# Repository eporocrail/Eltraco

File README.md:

Aim is to develop a switching and signaling system for model railroad track control.
  Communication is wireless.

  To disconnect the decoder from the controlling software in space and time the MOSQUITTO
  MQTT broker is used.

  Hardware setup is as simple as possible. In stead of having one hardware module for diffferent applications
  the design aims for three different PCB's specific to task where the Wemos has to be slotted into.

  Sofware is modularised. It is gathered into one software package. The functionality of each separate decoder
  is configured by means of a website genrated by the decoder.

  *********************************************************************************************

  Target platform is Wemos D1 mini.

  11 digital input/output pins, all pins have interrupt/pwm/I2C/one-wire supported(except D0)
  1 analog input(3.2V max input)
  a Micro USB connection
  compatible with Arduino IDE.
  pins are active LOW but the Arduino IDE inverts this.

  All of the IO pins run at 3.3V:
  A levelshifter or voltage divider is required.

  For a relay a pin is followed by a transistor/IC. A relay is driven with 5V.

  For a sensor or servo each pin is followed by a 330R resistor to limit current to 10 mA.

  eltraco decoder     Function

  eltraco sensor decoder    Scanning 9 sensors
  eltraco switch decoder    Controlling 8 outputs
  eltraco turnout decoder   Controlling 2 turnouts

  GPIO usage:

  Decoder  pins     function

  Sensor   D0 .. D7     digital sensor
  
           A0           analogue sensor

  Switch   D0 .. D7     output (switch)

  Double   D0    relais 1
  
  Turnout  D1    current detector 1
           
           D2    current detector 2
           
           D3    not used
           
           D4    not used
           
           D5    relais 2
           
           D6    servo 1
           
           D7    servo 2
           
           D8    not used
           
           A0    not used
           
  Single   D0    relais 1
  
  Turnout  D1    current detector 1
           
           D2    sensor
           
           D3    sensor
           
           D4    sensor
           
           D5    sensor
           
           D6    servo 1
           
           D7    not used
           
           D8    not used
           
           A0    not used         

  ROCNET PROTOCOL

  packet payload content:
  byte 1  : groupId
  
  byte 2  : receiveIdH
  
  byte 3  : receiveIdL
  
  byte 4  : sendIdH
  
  byte 5  : sendIdL
  
  byte 6  : group
  
  byte 7  : code
  
  byte 8  : length
  
  byte 9  : data1
  
  byte 10 : data2
  
  byte 11 : data3
  
  byte 12 : data4

  --byte 1 only used for large network. Normally 0.

  --byte 2 only used when more than 255 decoders. Normally 0.

  --byte 3 Rocrail Server default Id is 1

  Broadcast Id = 0
  
  Decoder   Id = 2 ... 255   Not used for switching decoder

  --byte 4 only used when more than 255 decoders. Normally 0.

  --byte 5 Rocrail Server default Id is 1

  Decoder Id   = 2 ... 255 with restrictions as described under "addressing"

  --byte 6

  groups
  code   description     remark                     MQTT topic
  
  0      Host            Rocrail                    rocnet/ht
  
  7      Clock Fast      Clock                      rocnet/ck
  
  8      Sensor          Position determination     rocnet/sr
  
  9      Output                                     rocnet/ot

  --byte 7

  Code:  bit 7 = 0
  
     bit 6 and bit 5 represent Type of code
     
     bit 4 .. 0:  5 bit command 0 .. 31

  Type: 0 - test
  
  1 - request
  
  2 - event
  
  3 - reply

  Sensor

  Actions
  code description data 1  data 2  data 3  data 4  data n
  1    report      addrH¹  addrL¹  status  port    identifier (RFID)

  ¹) Address of the reporting loco.
  The sensor ID is set in the header; Sender.

  Output

  Type   Value
  
  switch   0
  
  light    1
  
  servo    2

  Actions
  code description data 1  data 2  data 3
  
  0      off       type    value   address
  
  1      on        type    value   address

  --byte 8 Netto number of following data bytes.

  At a speed of 200 KmH a loc runs 64 mm per second in scale H0 and 35 mm per second in scale N.
  To come to a reliable detection reaction a point sensor must be scanned at least 20 times per second in H0
  and at least 10 times per second in scale N.

  For scale H0 scan delay should be not larger than 50 miliseconds and for scale N not larger
  than 100 miliseconds. Default will be 20.

  The Wemos Module needs no 3.3V power supply. To the 5V pin external powersupply can be connected.

  Addressing:

  Addressing falls apart in a WiFi address, being an IP-address and a Rocnet address.

  Rocnet:

  In the Rocnet protocol (IdH*256 + IdL) represents the Rocnet Node Number. This number ranges from 1 .. 65536.
  It represents the "Bus" number.
  Depending on the function performed the I/O pin of the decoder is addressed with "data3" for
  "output" functions or "data4" for "sensor" functions. Turnouts are controlled with an "output" function.
  The values of data3/data4 are in rocrail inserted in field "Address"

  For eltraco an I/O pin is addressed by the combination of receiveIdL and data3/data4.
  This way each individual pin of each individual decoder can be addressed.

  A second way to address an IO pin is using a "fixed" receiveIdL and discriminating by means of data3/data4.
  Using this method provides in eltraco the possibility to address 255 turnouts by a consecutive number only.
  The default receiveIdL of Rocrail is "9". This receiveIdL is used to control turnouts. These addresses are
  used by the servo-tool to adjust the servo of a turnout.

  IP-address:
  The following IP-adress range is available:
  192.168.xxx.xxx

  IP-addres: Router 192.168.xxx.251
  
             Configuration website 192.168.xxx.252
             
             Command Station       192.168.xxx.253
             
             Mosquitto             192.168.xxx.254

  For the decoders are available 192.168.xxx.2 - 192.168.2.250

  Each decoder is allocated a unique IP-address out of the range 192.168.xxx.2 - 192.168.2.250.
  The last triplet is the Rocrail "Bus" number.

  Single turnout decoder:

Each decoder controls 1 turnout and reports occupation of it.

For the turnout decoder occupation of the turnout is reported at "Address" 1.

Table: Switches tab Interface - the last part of the IP-address is inserted into field "Bus"
       "1" is inserted into field "Address".
       e.g. (192.168.0.154 turnout is inserted as Bus 154 Address 1)

Table: Sensor tab Interface - the last part of the IP-address is inserted into field "Bus"
       "1" is inserted into field "Address". The external sensors report using "Address" numbers 2 .. 5.
       e.g. (192.168.0.154 turnout is inserted as Bus 154 Address 1, the second external sensor of the same
       decoder is inserted as Bus 154 Address 3)

Double turnout decoder:

Each decoder controls 2 turnouts and reports occupation of them.

For the turnout decoder occupation of the first turnout is reported at "Address" 1 and of the second
turnout at "Address" 2.

Table: Switches tab Interface - the last part of the IP-address is inserted into field "Bus"
       For the first turnout "1" is inserted into field "Address". For the second one "2" is inserted
       e.g. (192.168.0.154 turnout 2 is inserted as Bus 154 Address 2)

Table: Sensor tab Interface - the last part of the IP-address is inserted into field "Bus"
       For the first turnout "1" is inserted into field "Address". For the second one "2" is inserted
       e.g. (192.168.0.154 turnout 2 is inserted as Bus 154 Address 2)

Operation

During testing it turned out that move orders from Rocrail arrived so fast that an ongoing movement was
interrupted. To cater for this, incoming turnout orders are stored into a buffer. When ongoing movement is concluded,
buffer content is converted into a turnout order and the next turnout starts moving.

Sensor decoder:
Each decoder has eight digital and one analogue sensor.

The sensors report using "Address" numbers 1 .. 9.
Use of the analogue sensor is to be programmed by the user.

Table: Sensor tab Interface - the last part of the IP-address is inserted into field "Bus"
       port number is inserted into field "Address"
       e.g. (192.168.0.076 sensor 5 is inserted as Bus 76 Address 5)

Operation

The state of the sensor is controlled by interrupt. Not only the state of the sensor but also the point in time of activation is stored.
If the sensor is still in the activated state after the debounce period has passed the Sensor Message is sent. 
The state of the sensor will change to "inactive" by interrupt. After the minimum activation time has passed this inactive state is signalled 
with a Sensor Message.

Interrupt reacts on changes to drive the sensor state.

D0 can NOT be used with Interrupt. This reduces the amount of interrupt driven sensors per module to 7. (D1 .. D7).

D0 has to be watched with "polling".

Switch decoder
Each decoder has eight outputs.

Each decoder is allocated a unique IP-address out of the range 192.168.xxx.2 - 192.168.2.250.
The last triplet is the Rocrail "Bus" number.

The outputs are switched using "Address" numbers 1 .. 8.

Table: Switches tab Interface - the last part of the IP-address is inserted into field "Bus"
       The individual port number is inserted into field "Address"
       e.g. (192.168.0.201 port 3 is inserted as Bus 201 Address 3)

Operation

Via configuration it is possible to have an output switched ON during 200 mSec. An additional relais attached to that
output can be used to control a solenoid activated device.

To signal the state of a switch, a sensor message is transmitted after each switch action. 

Configuration of decoder

The Wemos module can be used in "ST" mode and "AP" mode simultaneously.
In "ST" mode it is possible to login onto an existing WiFi network for normal operations.
In "AP" mode it is possible to generate its own WiFi network. This network is used for configuration of the decoder.
Each module has its own configuration webserver on a shared WiFi configuration network with its own IP address.

The websever is based on the "EmbAJAX" library. This library facilitates dataexchange between webserver on the decoder
and a browser on a client. The user experience is as much as possible comparable with webservers on PC like hardware.

Configuration data and servo angles are stored in EEPROM.
Allocation of EEPROM memory to variables has to be planned.
  location variable
      0    AngleA1
      1    AngleB1
      2    Delay1
      3    Swap1
      4    AngleA2
      5    AngleB2
      6    Delay2
      7    Swap2
      8    decoderType
      9    debugFlag

  GENERALOFFSET+ 0 .. 25 ST WiFi SSID
  
  GENERALOFFSET + SSIDOFFSET + 0 .. 8 ST WiFi Password
  
  GENERALOFFSET + SSIDOFFSET + PWDOFFSET + 0 .. 6 ST WiFi IP address triplets
  
  GENERALOFFSET + SSIDOFFSET + PWDOFFSET + IPOFFSET + 0 .. 8 Output puls 
  
  GENERALOFFSET + SSIDOFFSET + PWDOFFSET + IPOFFSET + OUTPUTOFFSET + 0 .. 8 Switch active puls length
  
  GENERALOFFSET + SSIDOFFSET + PWDOFFSET + IPOFFSET + OUTPUTOFFSET + PULSLENGTHOFFSET+ 0 .. 8 Output sensor message

  GENERALOFFSET      - 20
  SSIDOFFSET         - 30
  PWDOFFSET          - 20
  IPOFFSET           - 10
  OUTPUTOFFSET        -10
  PULSLENGTHOFFSET    -20
  OUTPUTSENSOROFFSET  -10

The ST WiFi password is generated out of "ELTRACO" and the decoderId.
The AP WiFi SSID is generated out of "ELTRACO" and the decoderID. This also aplies to the related password.

There are two ways to transfer Software to the decoder.
Via USB cable and after inital software installation also "Over The Air"(OTA).
Each decoder has its own OTA name which is generated outof "ELTRACO" and the decoderId.

Author: E. Postma

November 2018

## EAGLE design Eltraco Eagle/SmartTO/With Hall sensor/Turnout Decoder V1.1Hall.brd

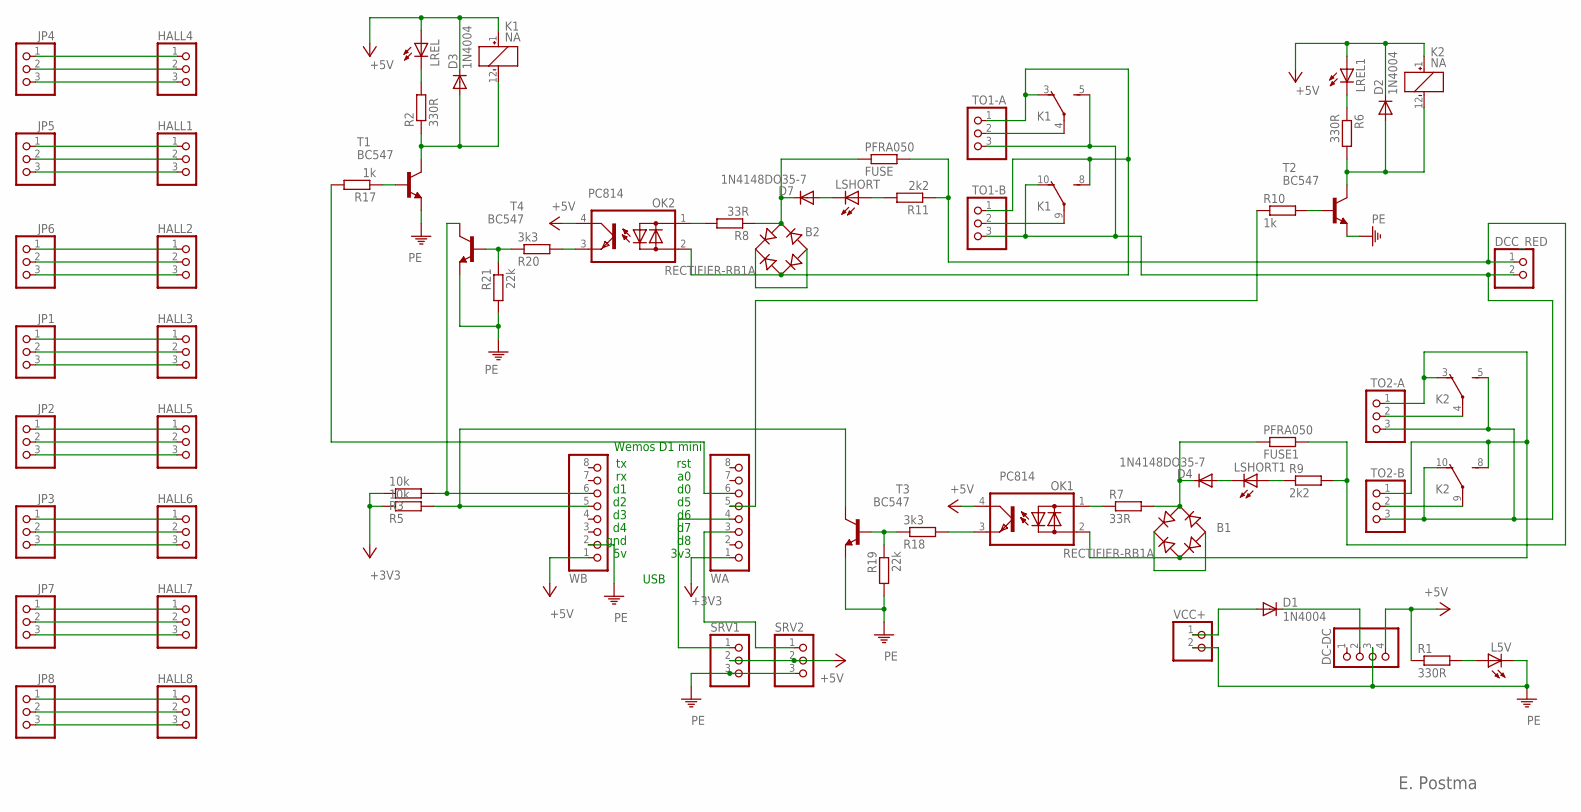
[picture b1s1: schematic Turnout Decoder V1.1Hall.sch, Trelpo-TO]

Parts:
B1, B2: RECTIFIER-RB1A; RB1A
D1, D2, D3: 1N4004; DO41-10
D4, D7: 1N4148DO35-7; DO35-7
DC-DC: PINHD-1X4; 1X04
DCC_RED: PINHD-1X2; 1X02
FUSE, FUSE1: PFRA050; 0414V
HALL1, HALL2, HALL3, HALL4, HALL5, HALL6, HALL7, HALL8: PINHD-1X3; 1X03
JP1, JP2, JP3, JP4, JP5, JP6, JP7, JP8: PINHD-1X3; 1X03
K1, K2: NA
L5V: LED3MM
LREL, LREL1: LED3MM
LSHORT, LSHORT1: LED3MM
OK1, OK2: PC814; DIL04
R1, R2, R6: 330R; 0207/7
R3, R5: 10k; 0207/7
R7, R8: 33R; 0207/7
R9, R11: 2k2; 0207/7
R10, R17: 1k; 0207/7
R18, R20: 3k3; 0207/7
R19, R21: 22k; 0207/7
SRV1, SRV2: PINHD-1X3; 1X03
T1, T2, T3, T4: BC547; TO92
TO1-A, TO1-B, TO2-A, TO2-B: PINHD-1X3; 1X03
VCC+: PINHD-1X2; 1X02
WA: PINHD-1X8; 1X08
WB: PINHD-1X8; 1X08

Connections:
+3V3: R3.1, R5.1, WA.1
+5V: D2.C, D3.C, DC-DC.4, K1.1 (+), K2.1 (+), LREL.A, LREL1.A, OK1.4 (C), OK2.4 (C), R1.1, SRV1.2, SRV2.2, WB.1
unnamed: HALL1.2, JP5.2
unnamed: LREL1.K (C), R6.1
unnamed: DCC_RED.1, FUSE.2, FUSE1.2, R9.2, R11.1
unnamed: D1.A, VCC+.1
unnamed: OK1.1 (AC1), R7.1
unnamed: LSHORT1.A, R9.1
unnamed: D4.A, LSHORT1.K (C)
unnamed: D2.A, K2.12 (-), R6.2, T2.3 (C)
unnamed: R10.2, T2.2 (B)
unnamed: B1.+, B1.-
unnamed: OK1.3 (E), R18.2
unnamed: LREL.K (C), R2.2
unnamed: K2.4, TO2-A.2
unnamed: B2.AC2, K1.3 (O), K1.8 (S), OK2.2 (AC2), TO1-A.1, TO1-B.1
unnamed: K2.9, TO2-B.2
unnamed: DCC_RED.2, K1.5 (S), K1.10 (O), K2.5 (S), K2.10 (O), TO1-A.3, TO1-B.3, TO2-A.3, TO2-B.3
unnamed: OK2.3 (E), R20.2
unnamed: B1.AC2, K2.3 (O), K2.8 (S), OK1.2 (AC2), TO2-A.1, TO2-B.1
unnamed: R3.2, T4.3 (C), WB.6
unnamed: B1.AC1, D4.C, FUSE1.1, R7.2
unnamed: OK2.1 (AC1), R8.2
unnamed: R5.2, T3.3 (C), WB.5
unnamed: B2.AC1, D7.C, FUSE.1, R8.1
unnamed: HALL1.1, JP5.1
unnamed: HALL1.3, JP5.3
unnamed: K1.4, TO1-A.2
unnamed: R18.1, R19.1, T3.2 (B)
unnamed: R20.1, R21.1, T4.2 (B)
unnamed: R17.2, WA.6
unnamed: HALL2.2, JP6.2
unnamed: SRV1.1, WA.4
unnamed: K1.9, TO1-B.2
unnamed: SRV2.1, WA.3
unnamed: R10.1, WA.5
unnamed: LSHORT.A, R11.2
unnamed: HALL2.1, JP6.1
unnamed: HALL2.3, JP6.3
unnamed: HALL3.2, JP1.2
unnamed: HALL3.1, JP1.1
unnamed: HALL3.3, JP1.3
unnamed: D7.A, LSHORT.K (C)
unnamed: B2.+, B2.-
unnamed: HALL5.2, JP2.2
unnamed: HALL5.1, JP2.1
unnamed: HALL5.3, JP2.3
unnamed: L5V.A, R1.2
unnamed: HALL6.2, JP3.2
unnamed: HALL6.1, JP3.1
unnamed: R17.1, T1.2 (B)
unnamed: D3.A, K1.12 (-), R2.1, T1.3 (C)
unnamed: HALL6.3, JP3.3
unnamed: HALL7.2, JP7.2
unnamed: HALL7.1, JP7.1
unnamed: HALL7.3, JP7.3
unnamed: HALL4.2, JP4.2
unnamed: HALL4.3, JP4.3
unnamed: HALL4.1, JP4.1
unnamed: D1.C, DC-DC.2
unnamed: HALL8.2, JP8.2
unnamed: HALL8.1, JP8.1
unnamed: HALL8.3, JP8.3
PE: DC-DC.3, L5V.K (C), R19.2, R21.2, SRV1.3, SRV2.3, T1.1 (E), T2.1 (E), T3.1 (E), T4.1 (E), VCC+.2, WB.2

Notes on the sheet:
rst
3v3
Wemos D1 mini
gnd
USB
E. Postma

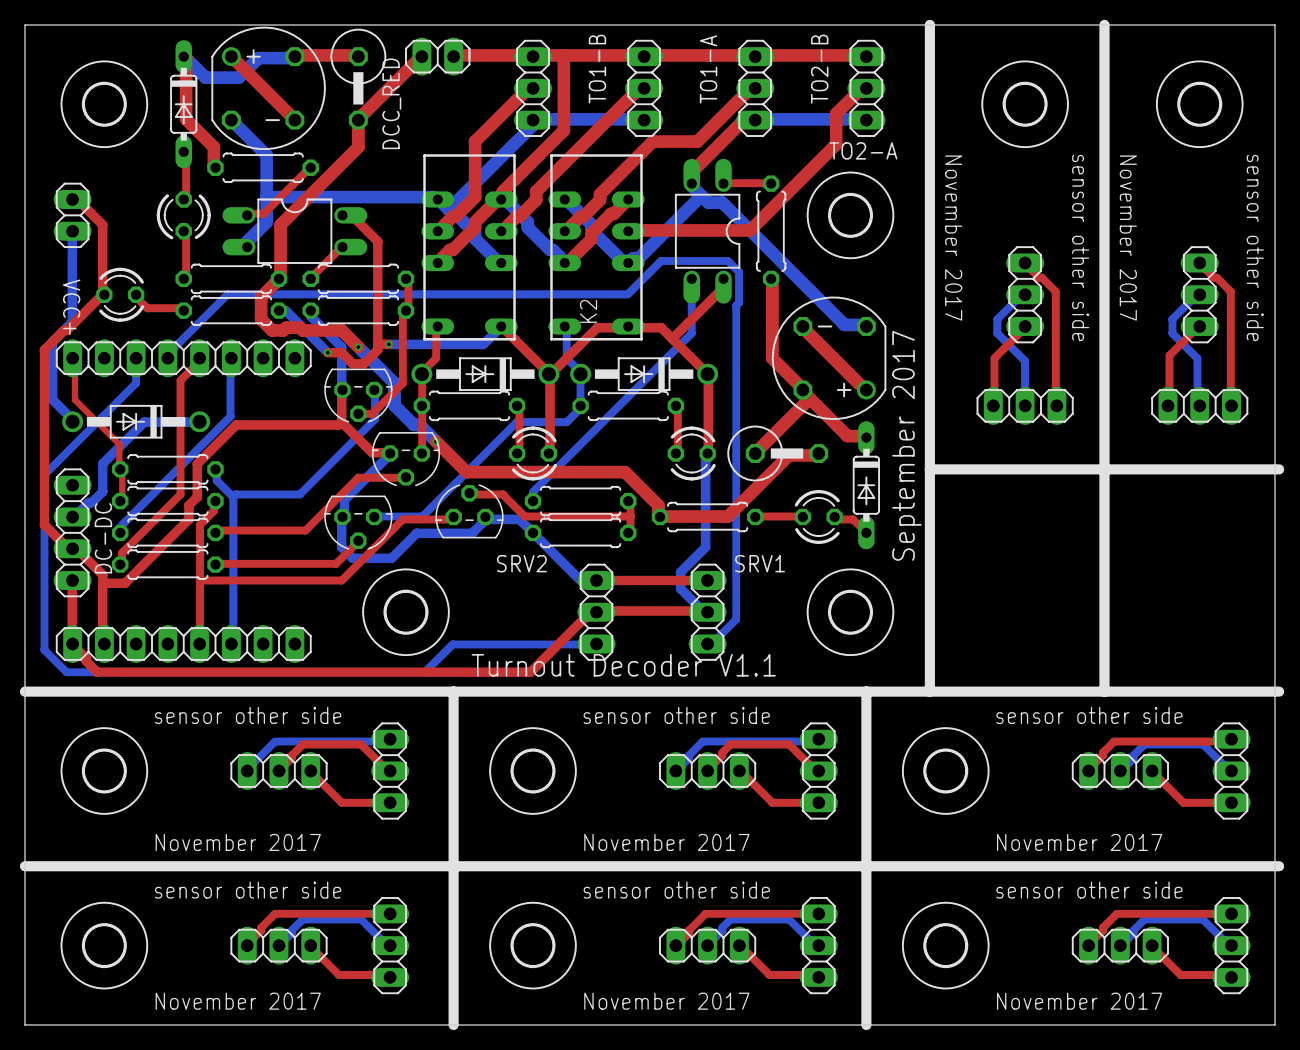
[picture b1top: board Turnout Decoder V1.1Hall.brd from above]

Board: 2 copper layers, 100.0 x 80.0 mm, 76 parts (0 on the bottom side), 64 nets.

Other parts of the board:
U$1, U$2, U$3, U$4, U$5, U$6, U$7, U$11, U$12, U$14, U$15, U$16: 3,2

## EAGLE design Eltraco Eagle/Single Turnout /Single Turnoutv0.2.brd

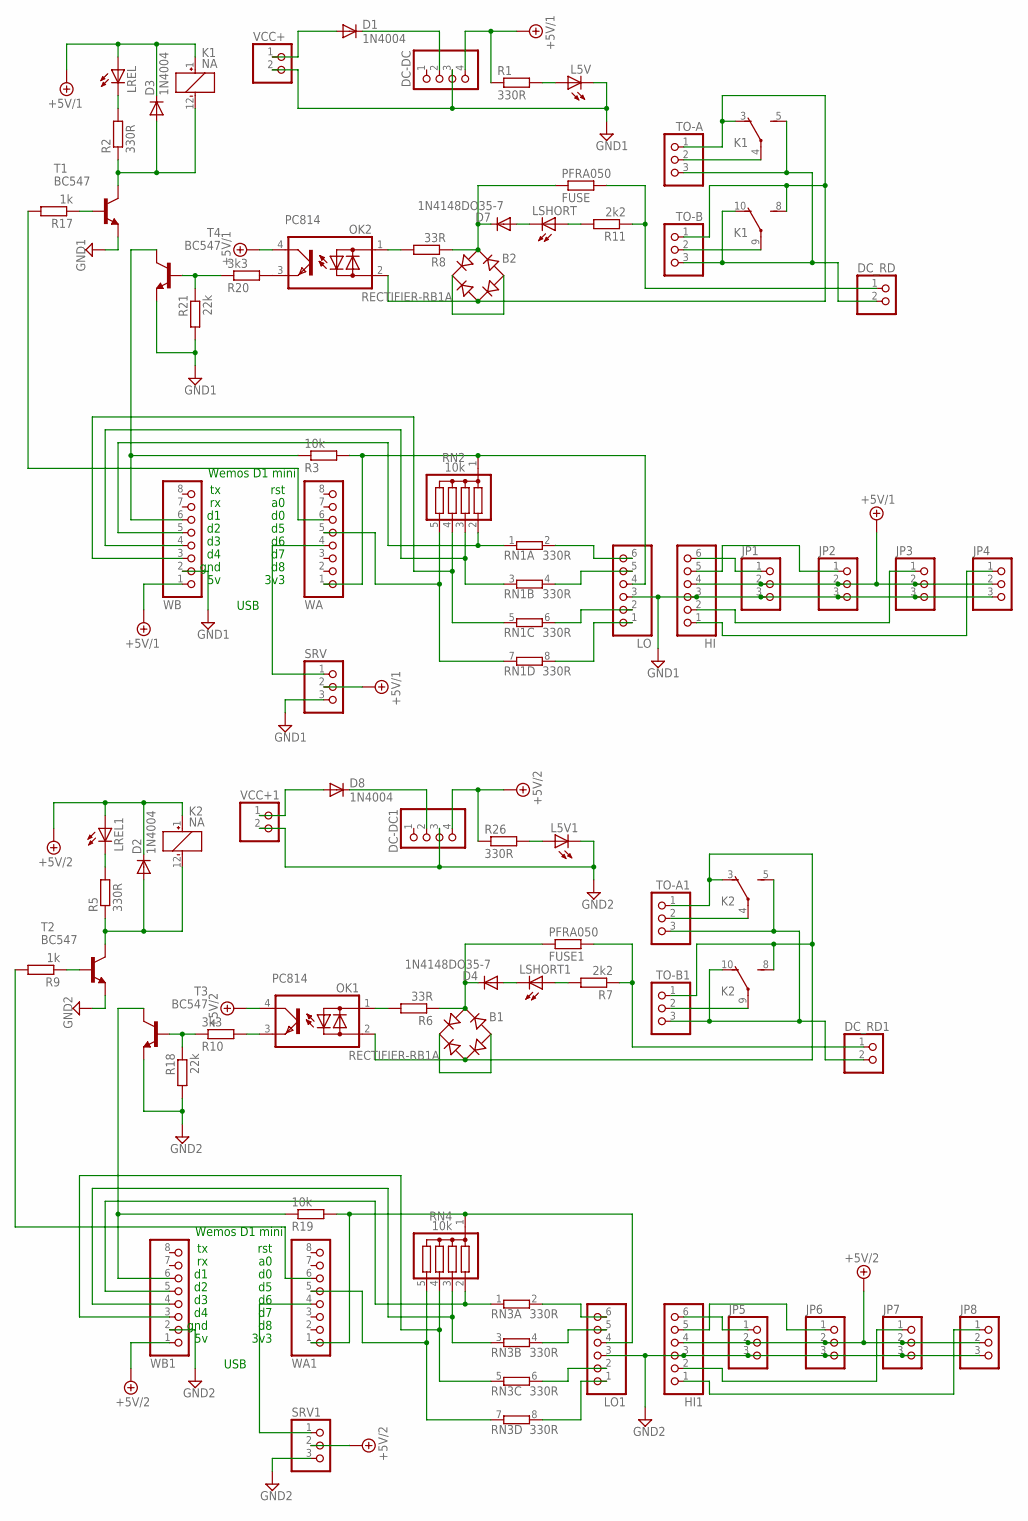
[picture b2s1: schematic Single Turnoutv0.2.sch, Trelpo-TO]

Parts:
B1, B2: RECTIFIER-RB1A; RB1A
D1, D2, D3, D8: 1N4004; DO41-10
D4, D7: 1N4148DO35-7; DO35-7
DC-DC, DC-DC1: PINHD-1X4; 1X04
DC_RD, DC_RD1: PINHD-1X2; 1X02
FUSE, FUSE1: PFRA050; 0414V
HI, HI1: PINHD-1X6; 1X06
JP1, JP2, JP3, JP4, JP5, JP6, JP7, JP8: PINHD-1X3; 1X03
K1, K2: NA
L5V, L5V1: LED3MM
LO, LO1: PINHD-1X6; 1X06
LREL, LREL1: LED3MM
LSHORT, LSHORT1: LED3MM
OK1, OK2: PC814; DIL04
R1, R2, R5, R26: 330R; 0207/7
R3, R19: 10k; 0207/7
R6, R8: 33R; 0207/7
R7, R11: 2k2; 0207/7
R9, R17: 1k; 0207/7
R10, R20: 3k3; 0207/7
R18, R21: 22k; 0207/7
RN1, RN3: 330R; SIL8
RN2, RN4: 10k; SIL5
SRV, SRV1: PINHD-1X3; 1X03
T1, T2, T3, T4: BC547; TO92
TO-A, TO-A1: PINHD-1X3; 1X03
TO-B, TO-B1: PINHD-1X3; 1X03
VCC+, VCC+1: PINHD-1X2; 1X02
WA, WA1: PINHD-1X8; 1X08
WB, WB1: PINHD-1X8; 1X08

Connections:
+5V/1: D3.C, DC-DC.4, HI.4, JP1.2, JP2.2, JP3.2, JP4.2, K1.1 (+), LREL.A, OK2.4 (C), R1.1, SRV.2, WB.1
+5V/2: D2.C, DC-DC1.4, HI1.4, JP5.2, JP6.2, JP7.2, JP8.2, K2.1 (+), LREL1.A, OK1.4 (C), R26.1, SRV1.2, WB1.1
GND1: DC-DC.3, HI.3, JP1.3, JP2.3, JP3.3, JP4.3, L5V.K (C), LO.3, R21.2, SRV.3, T1.1 (E), T4.1 (E), VCC+.2, WB.2
GND2: DC-DC1.3, HI1.3, JP5.3, JP6.3, JP7.3, JP8.3, L5V1.K (C), LO1.3, R18.2, SRV1.3, T2.1 (E), T3.1 (E), VCC+1.2, WB1.2
unnamed: LO.4, R3.2, RN2.1, WA.1
unnamed: LO.6, RN1.2
unnamed: DC_RD.1, FUSE.2, R11.1
unnamed: D1.A, VCC+.1
unnamed: R3.1, T4.3 (C), WB.6
unnamed: LREL1.K (C), R5.2
unnamed: OK1.1 (AC1), R6.2
unnamed: LSHORT1.A, R7.2
unnamed: D4.A, LSHORT1.K (C)
unnamed: D2.A, K2.12 (-), R5.1, T2.3 (C)
unnamed: R9.1, T2.2 (B)
unnamed: LREL.K (C), R2.2
unnamed: B1.+, B1.-
unnamed: B2.AC2, K1.3 (O), K1.8 (S), OK2.2 (AC2), TO-A.1, TO-B.1
unnamed: K2.4, TO-A1.2
unnamed: DC_RD.2, K1.5 (S), K1.10 (O), TO-A.3, TO-B.3
unnamed: OK2.3 (E), R20.2
unnamed: K2.9, TO-B1.2
unnamed: B1.AC2, K2.3 (O), K2.8 (S), OK1.2 (AC2), TO-A1.1, TO-B1.1
unnamed: B1.AC1, D4.C, FUSE1.1, R6.1
unnamed: OK2.1 (AC1), R8.2
unnamed: DC_RD1.2, K2.5 (S), K2.10 (O), TO-A1.3, TO-B1.3
unnamed: B2.AC1, D7.C, FUSE.1, R8.1
unnamed: LO.5, RN1.4 (2)
unnamed: HI.2, JP3.1
unnamed: K1.4, TO-A.2
unnamed: DC_RD1.1, FUSE1.2, R7.1
unnamed: R20.1, R21.1, T4.2 (B)
unnamed: R17.2, WA.6
unnamed: HI.5, JP2.1
unnamed: SRV.1, WA.4
unnamed: K1.9, TO-B.2
unnamed: SRV1.1, WA1.4
unnamed: R10.1, R18.1, T3.2 (B)
unnamed: LSHORT.A, R11.2
unnamed: HI.6, JP1.1
unnamed: RN1.3 (1), RN2.3, WB.4
unnamed: RN1.1, RN2.2, WB.5
unnamed: HI1.2, JP7.1
unnamed: HI1.5, JP6.1
unnamed: D7.A, LSHORT.K (C)
unnamed: B2.+, B2.-
unnamed: HI1.6, JP5.1
unnamed: RN1.5 (1), RN2.4, WB.3
unnamed: RN1.7 (1), RN2.5, WA.5
unnamed: L5V.A, R1.2
unnamed: RN3.5 (1), RN4.4, WB1.3
unnamed: LO1.4, R19.2, RN4.1, WA1.1
unnamed: R17.1, T1.2 (B)
unnamed: D3.A, K1.12 (-), R2.1, T1.3 (C)
unnamed: RN3.7 (1), RN4.5, WA1.5
unnamed: HI1.1, JP8.1
unnamed: LO.2, RN1.6 (2)
unnamed: RN3.3 (1), RN4.3, WB1.4
unnamed: RN3.1, RN4.2, WB1.5
unnamed: LO.1, RN1.8 (2)
unnamed: LO1.6, RN3.2
unnamed: D1.C, DC-DC.2
unnamed: LO1.5, RN3.4 (2)
unnamed: LO1.2, RN3.6 (2)
unnamed: HI.1, JP4.1
unnamed: R9.2, WA1.6
unnamed: OK1.3 (E), R10.2
unnamed: L5V1.A, R26.2
unnamed: R19.1, T3.3 (C), WB1.6
unnamed: LO1.1, RN3.8 (2)
unnamed: D8.A, VCC+1.1
unnamed: D8.C, DC-DC1.2

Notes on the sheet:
rst
3v3
Wemos D1 mini
gnd
USB

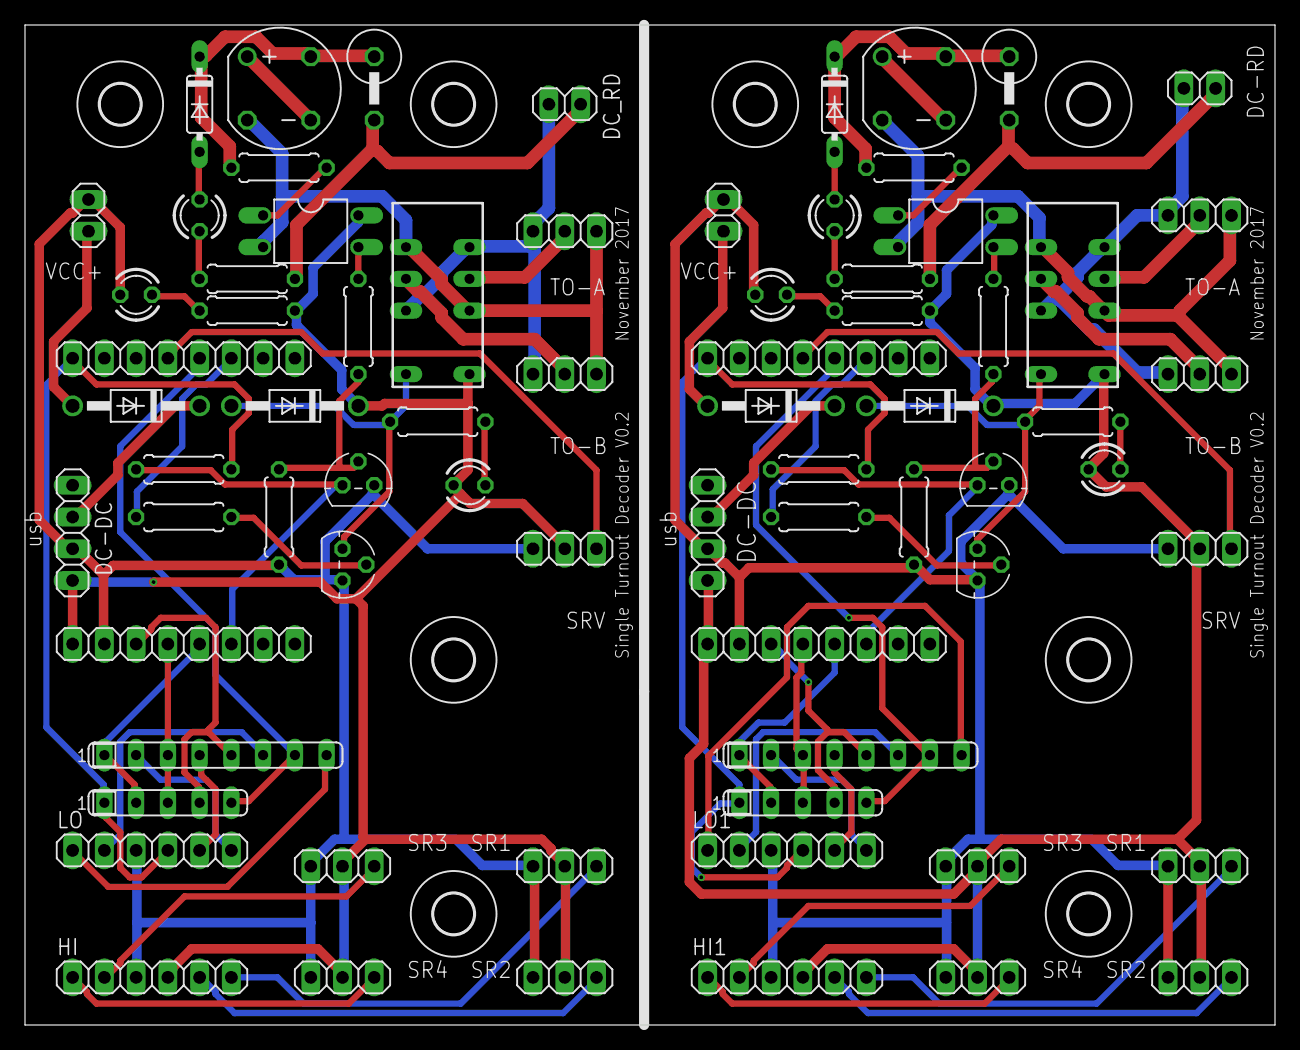
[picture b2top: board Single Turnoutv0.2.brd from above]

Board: 2 copper layers, 100.0 x 80.0 mm, 80 parts (0 on the bottom side), 72 nets.

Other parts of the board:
U$1, U$2, U$3, U$4, U$5, U$6, U$7, U$9: 3,2

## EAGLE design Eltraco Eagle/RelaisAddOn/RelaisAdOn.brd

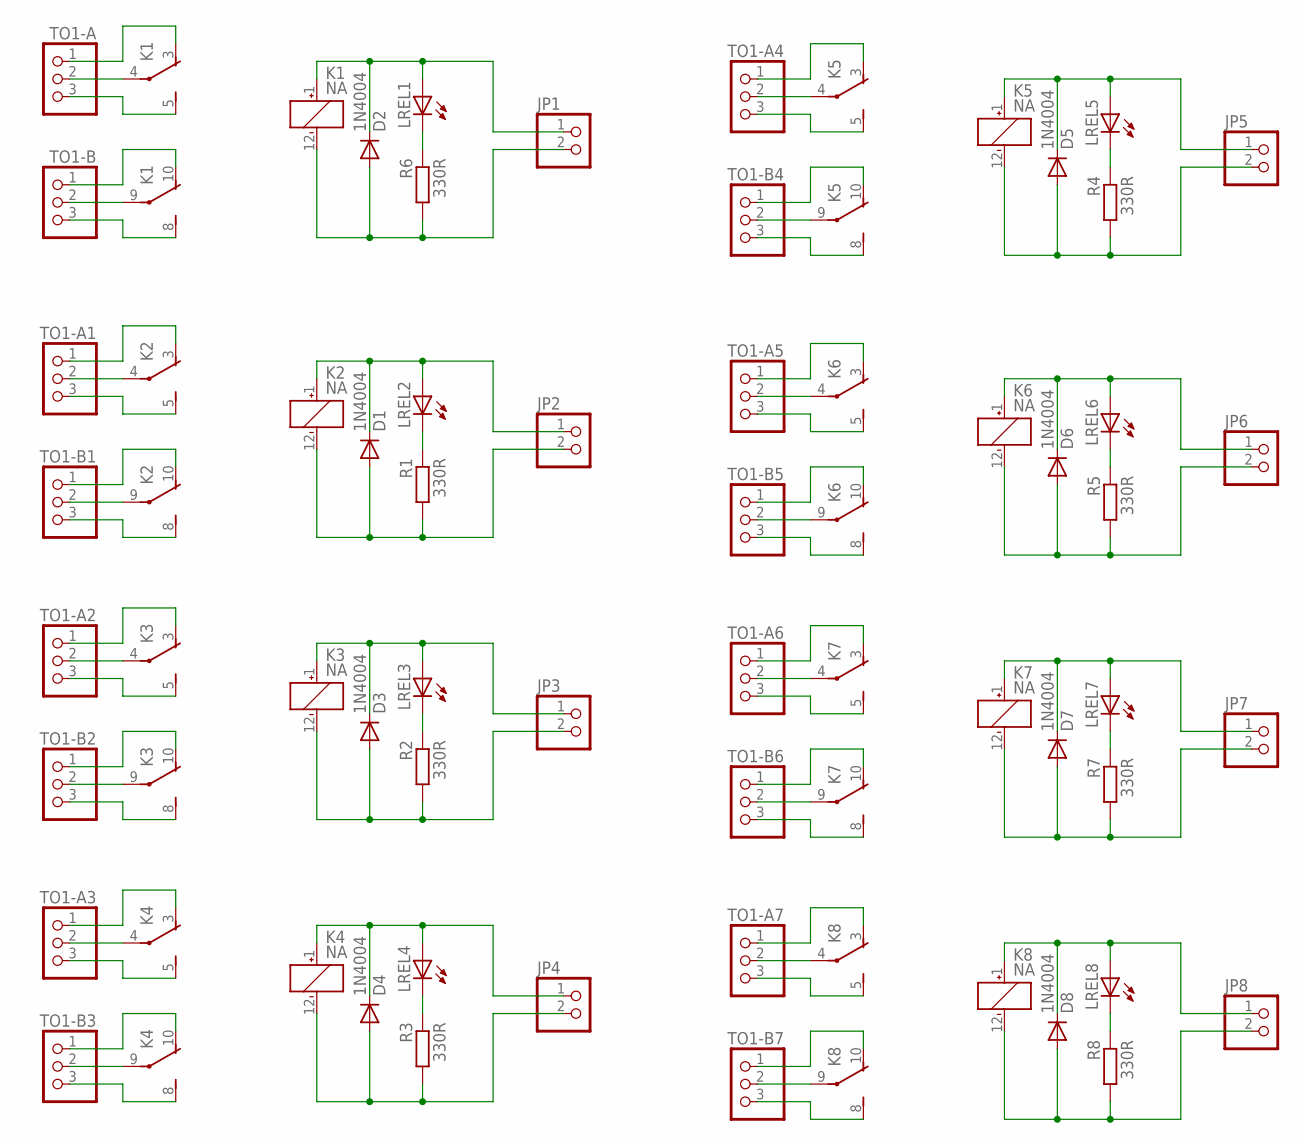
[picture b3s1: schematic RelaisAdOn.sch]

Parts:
D1, D2, D3, D4, D5, D6, D7, D8: 1N4004; DO41-10
JP1, JP2, JP3, JP4, JP5, JP6, JP7, JP8: PINHD-1X2; 1X02
K1, K2, K3, K4, K5, K6, K7, K8: NA
LREL1, LREL2, LREL3, LREL4, LREL5, LREL6, LREL7, LREL8: LED3MM
R1, R2, R3, R4, R5, R6, R7, R8: 330R; 0207/7
TO1-A, TO1-A1, TO1-A2, TO1-A3, TO1-A4, TO1-A5, TO1-A6, TO1-A7, TO1-B, TO1-B1, TO1-B2, TO1-B3, TO1-B4, TO1-B5, TO1-B6, TO1-B7: PINHD-1X3; 1X03

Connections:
unnamed: K1.4, TO1-A.2
unnamed: LREL1.K (C), R6.1
unnamed: K1.9, TO1-B.2
unnamed: K1.8 (S), TO1-B.3
unnamed: K1.10 (O), TO1-B.1
unnamed: K1.3 (O), TO1-A.1
unnamed: K1.5 (S), TO1-A.3
unnamed: D2.A, JP1.2, K1.12 (-), R6.2
unnamed: D2.C, JP1.1, K1.1 (+), LREL1.A
unnamed: LREL2.K (C), R1.1
unnamed: D1.A, JP2.2, K2.12 (-), R1.2
unnamed: D1.C, JP2.1, K2.1 (+), LREL2.A
unnamed: K2.4, TO1-A1.2
unnamed: K2.9, TO1-B1.2
unnamed: K2.8 (S), TO1-B1.3
unnamed: K2.10 (O), TO1-B1.1
unnamed: K2.3 (O), TO1-A1.1
unnamed: K2.5 (S), TO1-A1.3
unnamed: LREL3.K (C), R2.1
unnamed: D3.A, JP3.2, K3.12 (-), R2.2
unnamed: D3.C, JP3.1, K3.1 (+), LREL3.A
unnamed: K3.4, TO1-A2.2
unnamed: K3.9, TO1-B2.2
unnamed: K3.8 (S), TO1-B2.3
unnamed: K3.10 (O), TO1-B2.1
unnamed: K3.3 (O), TO1-A2.1
unnamed: K3.5 (S), TO1-A2.3
unnamed: LREL4.K (C), R3.1
unnamed: D4.A, JP4.2, K4.12 (-), R3.2
unnamed: D4.C, JP4.1, K4.1 (+), LREL4.A
unnamed: K4.4, TO1-A3.2
unnamed: K4.9, TO1-B3.2
unnamed: K4.8 (S), TO1-B3.3
unnamed: K4.10 (O), TO1-B3.1
unnamed: K4.3 (O), TO1-A3.1
unnamed: K4.5 (S), TO1-A3.3
unnamed: LREL5.K (C), R4.1
unnamed: D5.A, JP5.2, K5.12 (-), R4.2
unnamed: D5.C, JP5.1, K5.1 (+), LREL5.A
unnamed: K5.4, TO1-A4.2
unnamed: K5.9, TO1-B4.2
unnamed: K5.8 (S), TO1-B4.3
unnamed: K5.10 (O), TO1-B4.1
unnamed: K5.3 (O), TO1-A4.1
unnamed: K5.5 (S), TO1-A4.3
unnamed: LREL6.K (C), R5.1
unnamed: D6.A, JP6.2, K6.12 (-), R5.2
unnamed: D6.C, JP6.1, K6.1 (+), LREL6.A
unnamed: K6.4, TO1-A5.2
unnamed: K6.9, TO1-B5.2
unnamed: K6.8 (S), TO1-B5.3
unnamed: K6.10 (O), TO1-B5.1
unnamed: K6.3 (O), TO1-A5.1
unnamed: K6.5 (S), TO1-A5.3
unnamed: LREL7.K (C), R7.1
unnamed: D7.A, JP7.2, K7.12 (-), R7.2
unnamed: D7.C, JP7.1, K7.1 (+), LREL7.A
unnamed: K7.4, TO1-A6.2
unnamed: K7.9, TO1-B6.2
unnamed: K7.8 (S), TO1-B6.3
unnamed: K7.10 (O), TO1-B6.1
unnamed: K7.3 (O), TO1-A6.1
unnamed: K7.5 (S), TO1-A6.3
unnamed: LREL8.K (C), R8.1
unnamed: D8.A, JP8.2, K8.12 (-), R8.2
unnamed: D8.C, JP8.1, K8.1 (+), LREL8.A
unnamed: K8.4, TO1-A7.2
unnamed: K8.9, TO1-B7.2
unnamed: K8.8 (S), TO1-B7.3
unnamed: K8.10 (O), TO1-B7.1
unnamed: K8.3 (O), TO1-A7.1
unnamed: K8.5 (S), TO1-A7.3

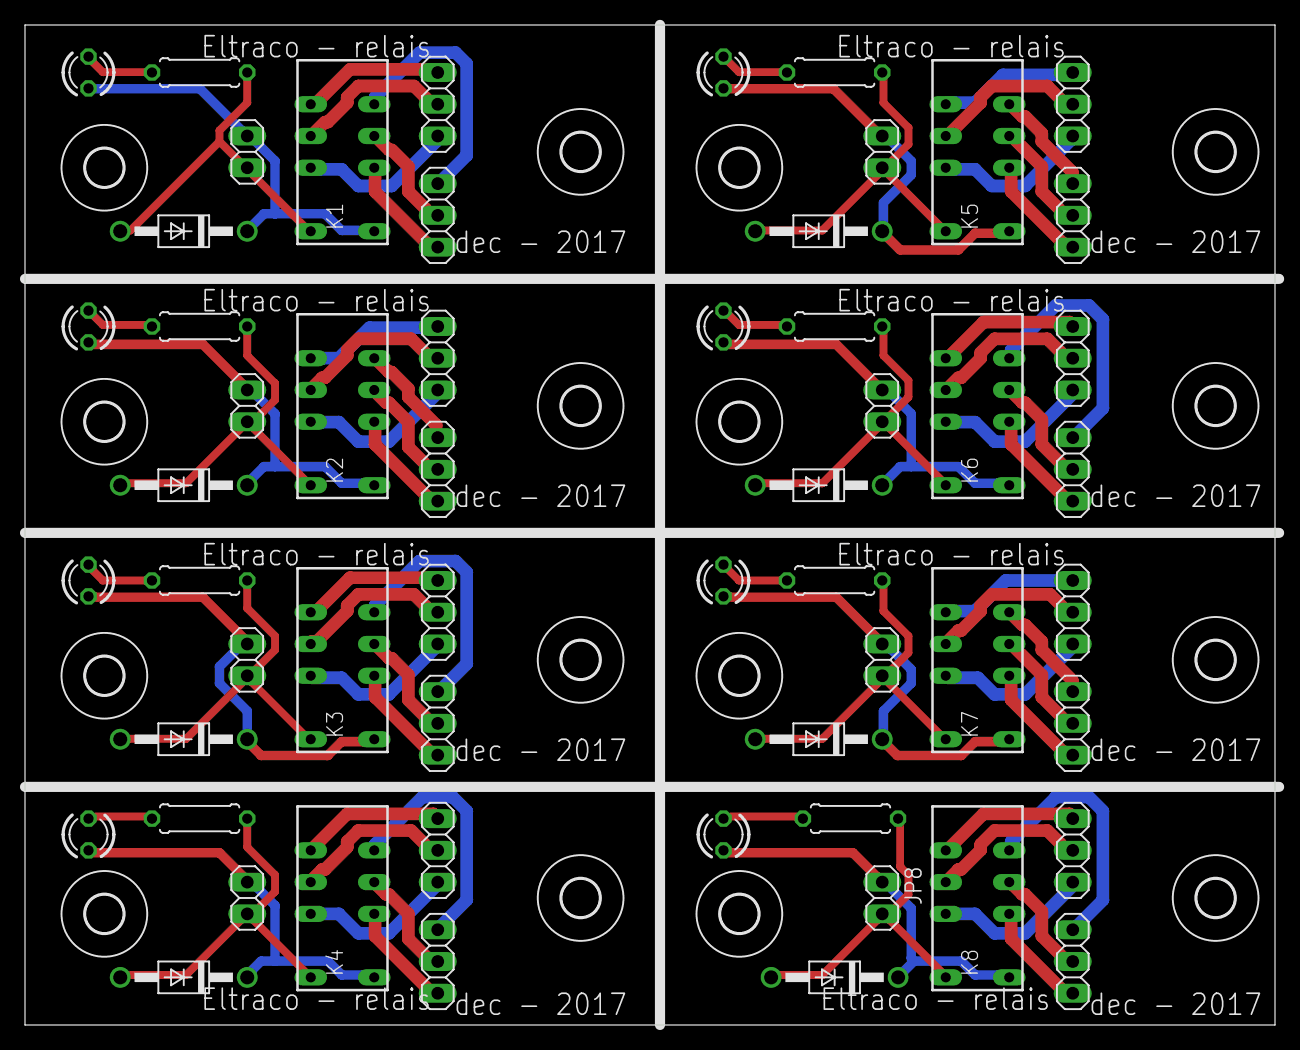
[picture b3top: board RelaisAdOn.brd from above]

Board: 2 copper layers, 100.0 x 80.0 mm, 72 parts (0 on the bottom side), 72 nets.

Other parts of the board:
U$1, U$2, U$3, U$4, U$5, U$6, U$7, U$8, U$9, U$10, U$11, U$12, U$13, U$14, U$15, U$16: 3,0

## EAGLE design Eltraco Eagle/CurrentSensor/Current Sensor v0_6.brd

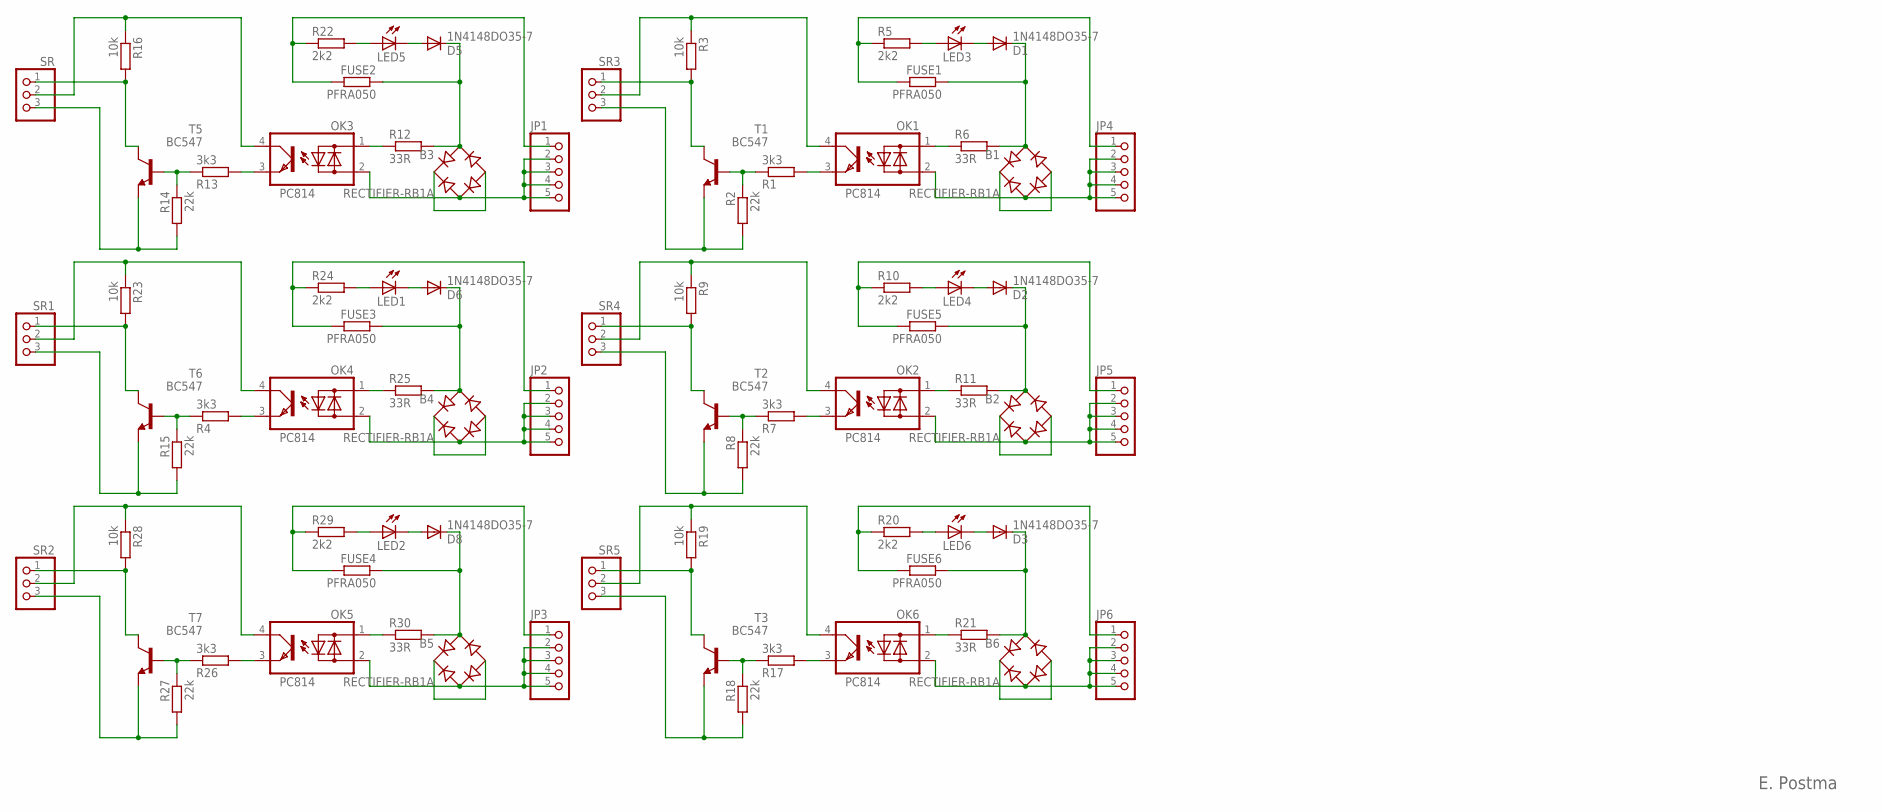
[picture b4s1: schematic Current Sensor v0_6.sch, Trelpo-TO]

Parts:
B1, B2, B3, B4, B5, B6: RECTIFIER-RB1A; RB1A
D1, D2, D3, D5, D6, D8: 1N4148DO35-7; DO35-7
FUSE1, FUSE2, FUSE3, FUSE4, FUSE5, FUSE6: PFRA050; 0414V
JP1, JP2, JP3, JP4, JP5, JP6: PINHD-1X5; 1X05
LED1, LED2, LED3, LED4, LED5, LED6: LED3MM
OK1, OK2, OK3, OK4, OK5, OK6: PC814; DIL04
R1, R4, R7, R13, R17, R26: 3k3; 0207/7
R2, R8, R14, R15, R18, R27: 22k; 0207/7
R3, R9, R16, R19, R23, R28: 10k; 0207/7
R5, R10, R20, R22, R24, R29: 2k2; 0207/7
R6, R11, R12, R21, R25, R30: 33R; 0207/7
SR, SR1, SR2, SR3, SR4, SR5: PINHD-1X3; 1X03
T1, T2, T3, T5, T6, T7: BC547; TO92

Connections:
unnamed: OK3.1 (AC1), R12.1
unnamed: OK1.1 (AC1), R6.1
unnamed: LED3.A, R5.2
unnamed: D1.A, LED3.K (C)
unnamed: B1.AC1, D1.C, FUSE1.1, R6.2
unnamed: B1.+, B1.-
unnamed: FUSE1.2, JP4.1, R5.1
unnamed: B1.AC2, JP4.2, JP4.3, JP4.4, JP4.5, OK1.2 (AC2)
unnamed: R1.1, R2.1, T1.2 (B)
unnamed: R3.2, SR3.1, T1.3 (C)
unnamed: OK1.3 (E), R1.2
unnamed: OK1.4 (C), R3.1, SR3.2
unnamed: R2.2, SR3.3, T1.1 (E)
unnamed: OK2.1 (AC1), R11.1
unnamed: LED4.A, R10.2
unnamed: D2.A, LED4.K (C)
unnamed: B2.AC1, D2.C, FUSE5.1, R11.2
unnamed: B2.+, B2.-
unnamed: FUSE5.2, JP5.1, R10.1
unnamed: B2.AC2, JP5.2, JP5.3, JP5.4, JP5.5, OK2.2 (AC2)
unnamed: R7.1, R8.1, T2.2 (B)
unnamed: R9.2, SR4.1, T2.3 (C)
unnamed: OK2.3 (E), R7.2
unnamed: LED5.A, R22.2
unnamed: D5.A, LED5.K (C)
unnamed: OK2.4 (C), R9.1, SR4.2
unnamed: R8.2, SR4.3, T2.1 (E)
unnamed: OK6.1 (AC1), R21.1
unnamed: LED6.A, R20.2
unnamed: B3.AC1, D5.C, FUSE2.1, R12.2
unnamed: D3.A, LED6.K (C)
unnamed: B6.AC1, D3.C, FUSE6.1, R21.2
unnamed: B6.+, B6.-
unnamed: FUSE6.2, JP6.1, R20.1
unnamed: B6.AC2, JP6.2, JP6.3, JP6.4, JP6.5, OK6.2 (AC2)
unnamed: B3.+, B3.-
unnamed: FUSE2.2, JP1.1, R22.1
unnamed: R13.1, R14.1, T5.2 (B)
unnamed: R16.2, SR.1, T5.3 (C)
unnamed: B3.AC2, JP1.2, JP1.3, JP1.4, JP1.5, OK3.2 (AC2)
unnamed: R17.1, R18.1, T3.2 (B)
unnamed: R19.2, SR5.1, T3.3 (C)
unnamed: OK3.3 (E), R13.2
unnamed: OK4.1 (AC1), R25.1
unnamed: OK3.4 (C), R16.1, SR.2
unnamed: OK6.3 (E), R17.2
unnamed: LED1.A, R24.2
unnamed: D6.A, LED1.K (C)
unnamed: OK6.4 (C), R19.1, SR5.2
unnamed: R18.2, SR5.3, T3.1 (E)
unnamed: B4.AC1, D6.C, FUSE3.1, R25.2
unnamed: B4.+, B4.-
unnamed: FUSE3.2, JP2.1, R24.1
unnamed: B4.AC2, JP2.2, JP2.3, JP2.4, JP2.5, OK4.2 (AC2)
unnamed: R4.1, R15.1, T6.2 (B)
unnamed: R23.2, SR1.1, T6.3 (C)
unnamed: OK4.3 (E), R4.2
unnamed: OK4.4 (C), R23.1, SR1.2
unnamed: R14.2, SR.3, T5.1 (E)
unnamed: R15.2, SR1.3, T6.1 (E)
unnamed: OK5.1 (AC1), R30.1
unnamed: LED2.A, R29.2
unnamed: D8.A, LED2.K (C)
unnamed: B5.AC1, D8.C, FUSE4.1, R30.2
unnamed: B5.+, B5.-
unnamed: FUSE4.2, JP3.1, R29.1
unnamed: B5.AC2, JP3.2, JP3.3, JP3.4, JP3.5, OK5.2 (AC2)
unnamed: R26.1, R27.1, T7.2 (B)
unnamed: R28.2, SR2.1, T7.3 (C)
unnamed: OK5.3 (E), R26.2
unnamed: OK5.4 (C), R28.1, SR2.2
unnamed: R27.2, SR2.3, T7.1 (E)

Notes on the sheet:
E. Postma

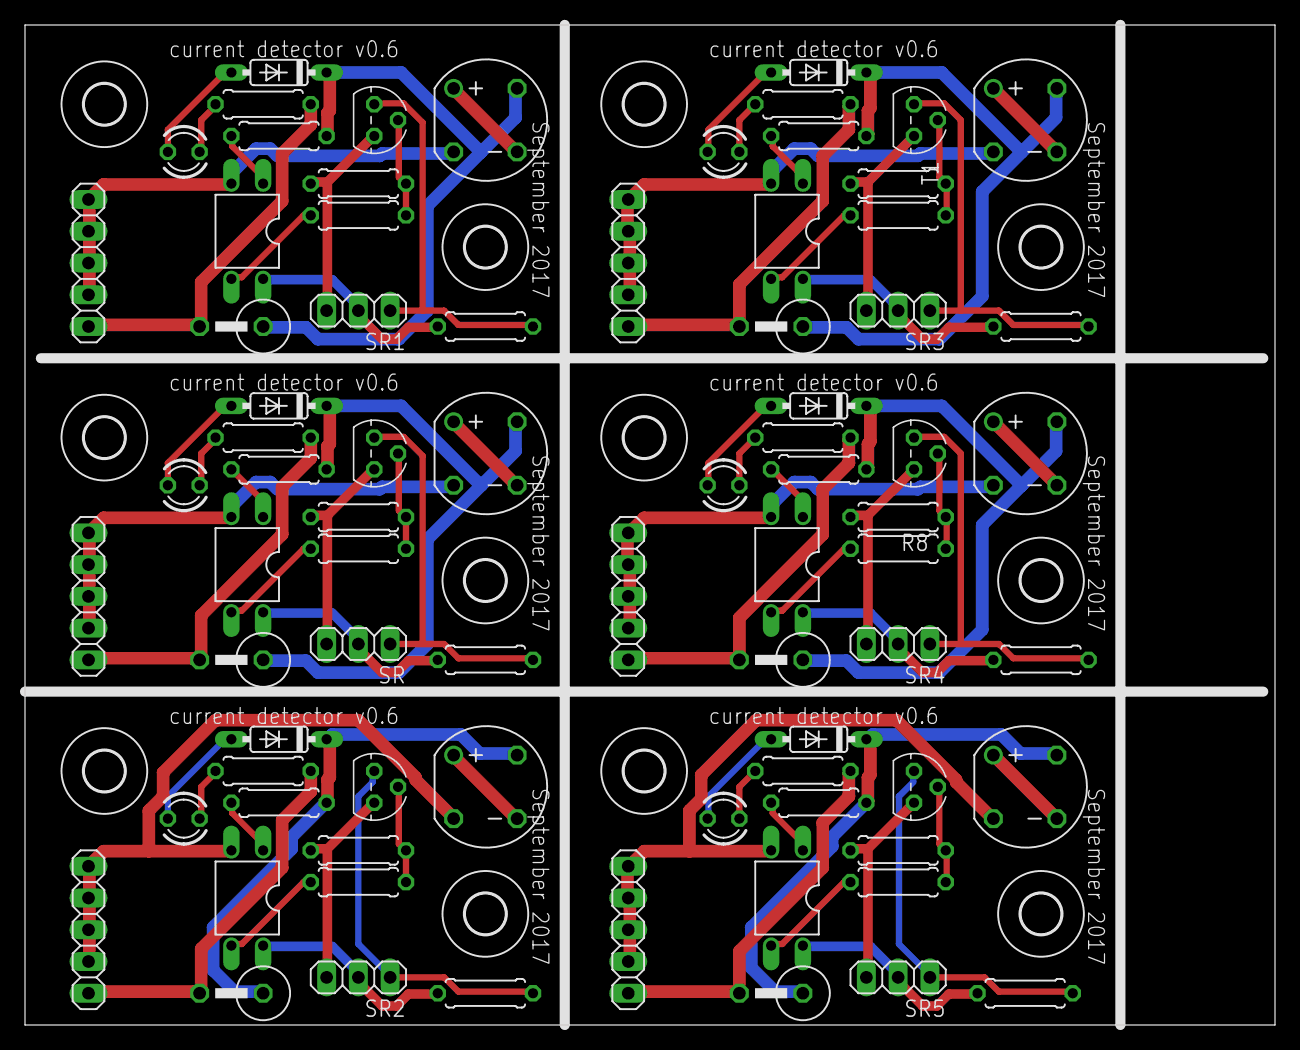
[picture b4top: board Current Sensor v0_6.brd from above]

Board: 2 copper layers, 100.0 x 80.0 mm, 90 parts (0 on the bottom side), 72 nets.

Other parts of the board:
U$1, U$2, U$3, U$4, U$5, U$6, U$7, U$8, U$9, U$10, U$11, U$12: 3,2
